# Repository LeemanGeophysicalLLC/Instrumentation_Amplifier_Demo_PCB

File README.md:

# Instrumentation_Amplifier_Demo_PCB
Instrumentation amplifier learning/demo PCB.

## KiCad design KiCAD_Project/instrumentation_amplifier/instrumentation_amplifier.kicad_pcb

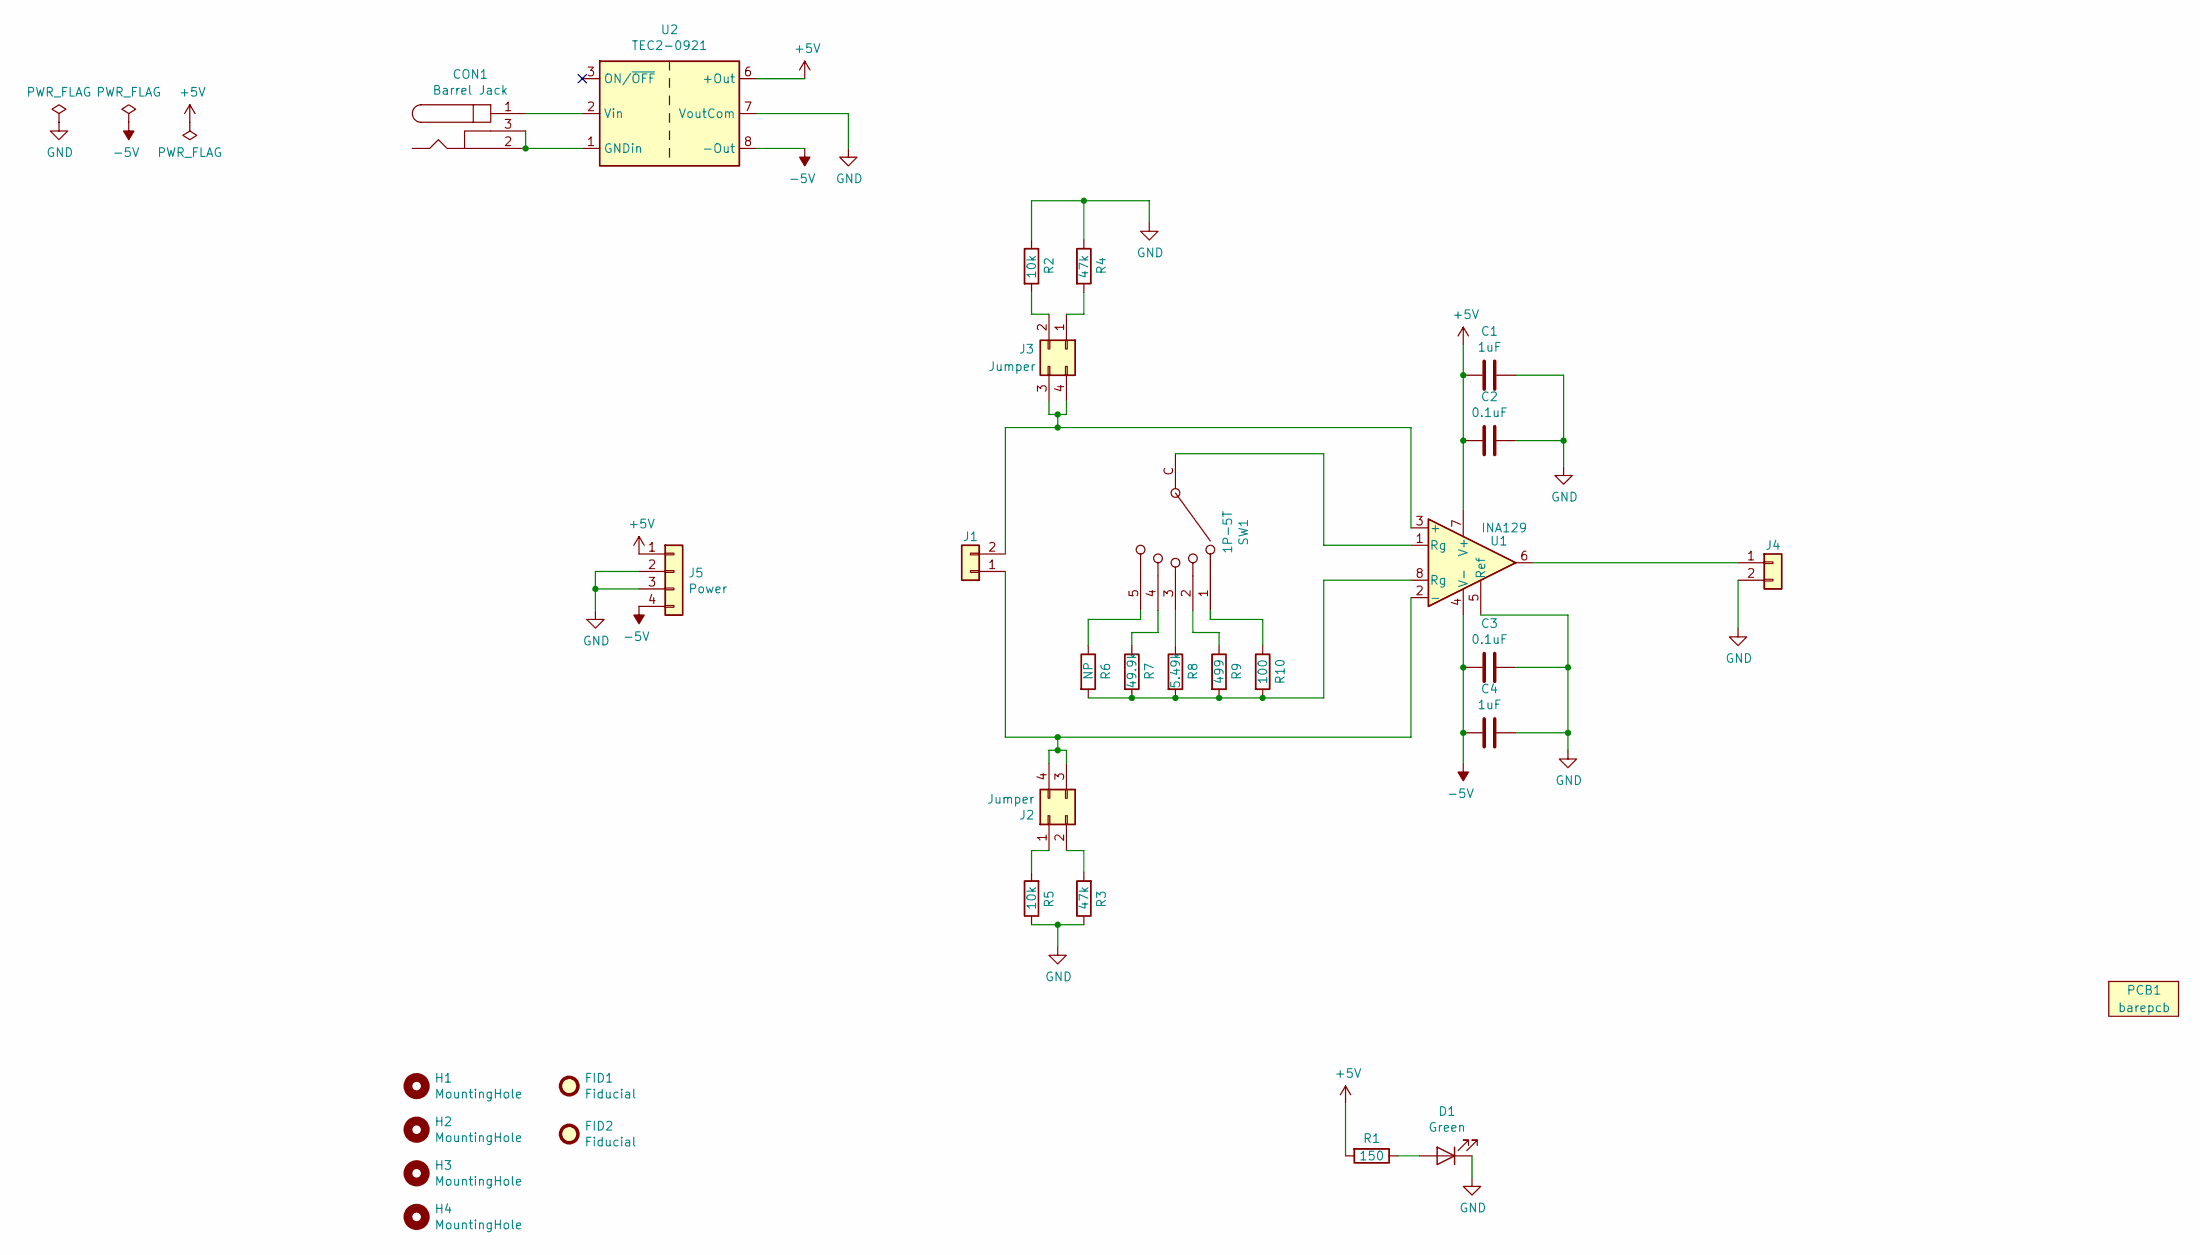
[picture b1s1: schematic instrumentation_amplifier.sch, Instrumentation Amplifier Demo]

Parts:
C1, C4: 1-0000018
C2, C3: 1-0000007
CON1: 1-0000001
D1: 1-0000598
FID1, FID2: Fiducial; Fiducial_1mm_Mask2mm
H1, H2, H3, H4: MountingHole; MountingHole_3.2mm_M3_ISO7380
J1, J4: 1-0000120
J2, J3: Jumper; PinHeader_2x02_P2.54mm_Vertical
J5: NP_Conn_01x04; PinHeader_1x04_P2.54mm_Vertical
PCB1: barepcb
R1: 1-0000008
R2, R5: 1-0000010
R3, R4: 1-0000011
R6: 1-0000006
R7: 1-0000851
R8: 1-0000177
R9: 1-0000179
R10: 1-0000112
SW1: 1-0000852
U1: 1-0000801
U2: 1-0000465

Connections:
+5V: C1.2, C2.2, J5.1, R1.2, U1.7 (V+), U2.6 (+Out)
-5V: C3.2, C4.2, J5.4, U1.4 (V-), U2.8 (-Out)
GND: C1.1, C2.1, C3.1, C4.1, D1.1 (K), J4.2, J5.2, J5.3, R2.1, R3.1, R4.1, R5.1, U1.5 (Ref), U2.7 (VoutCom)
unnamed: CON1.1, U2.2 (Vin)
unnamed: CON1.2, CON1.3, U2.1 (GNDin)
unnamed: D1.2 (A), R1.1
unnamed: J1.1, J2.3, J2.4, U1.2 (-)
unnamed: J1.2, J3.3, J3.4, U1.3 (+)
unnamed: J2.1, R5.2
unnamed: J2.2, R3.2
unnamed: J3.1, R4.2
unnamed: J3.2, R2.2
unnamed: J4.1, U1.6
unnamed: R6.1, SW1.5
unnamed: R7.1, SW1.4
unnamed: R8.1, SW1.3
unnamed: R9.1, SW1.2
unnamed: R10.1, SW1.1
unnamed: R6.2, R7.2, R8.2, R9.2, R10.2, U1.8 (Rg)
unnamed: SW1.C, U1.1 (Rg)

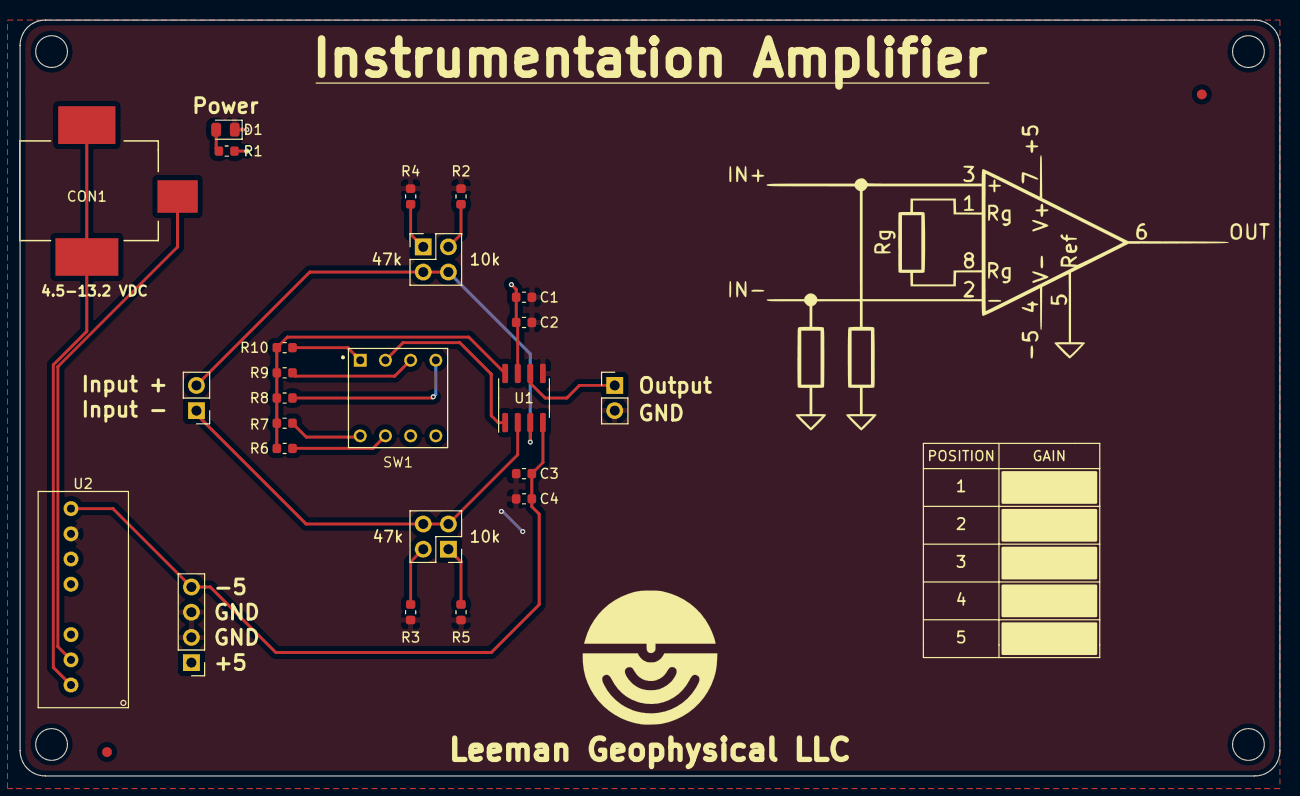
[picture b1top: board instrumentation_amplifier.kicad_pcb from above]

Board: 2 copper layers, 127.0 x 76.2 mm, 31 parts (0 on the bottom side), 20 nets.

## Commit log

2021-04-16 Initial schematic capture
2021-04-16 Initial Layout
2021-04-19 Layout Fixup
2021-04-20 Switch Fixup
2021-04-22 Production ready Rev 1.0
2021-05-04 Add STENCIL Folder and File
2021-05-06 Fixed jumper resistor location, silk screens, fixed J2
2021-05-06 Fixed schematic issue
2021-05-11 Rev 1.1 Production
